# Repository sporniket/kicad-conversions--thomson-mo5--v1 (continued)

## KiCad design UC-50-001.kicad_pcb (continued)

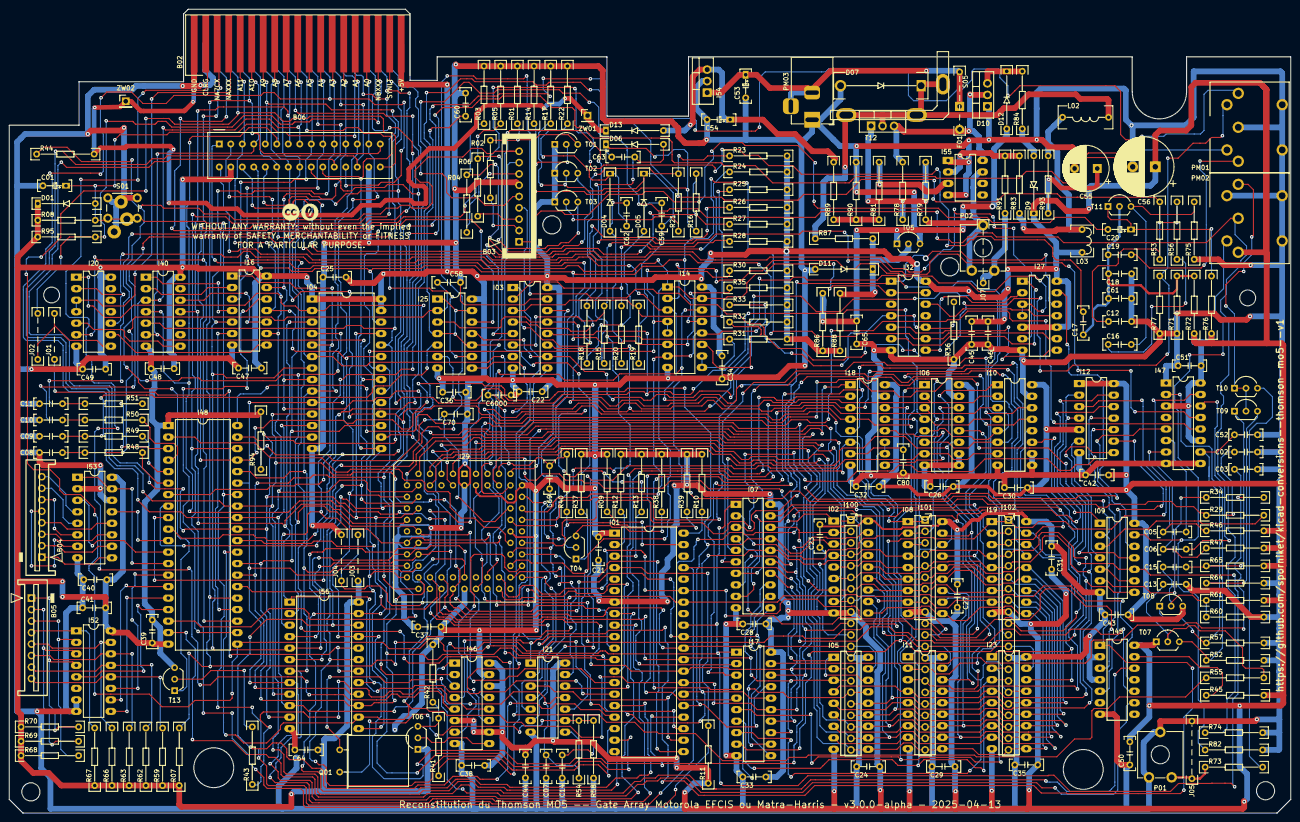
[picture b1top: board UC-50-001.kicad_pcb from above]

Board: 2 copper layers, 283.0 x 177.5 mm, 253 parts (1 on the bottom side), 233 nets.

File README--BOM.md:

# Bill of material

> On A4 sized sheets of paper, best printed using landscape format, zooming at most 75%.

## Capacitors

### Non polarized

|Quantity|Designators|Value|Comment|Suggestion|
|---|---|---|---|---|
|5|C02, C03, C05, C15, C60|100pF|Radial, pitch 5,08mm/200mils|Vishay K101K10X7RH5UH5|
|32|C06, C21, C22, C23, C24, C25, C26, C27, C28, C29, C30, C31, C32, C33, C34, C35, C36, C37, C38, C39, C40, C41, C42, C43, C44, C45, C46, C47, C48, C49, C50, C51|47nF|Radial, pitch 5,08mm/200mils|Vishay K473K10X7RF5UH5|
|2|C07, C14|120pF|Radial, pitch 5,08mm/200mils|Vishay K121K10X7RF5UH5|
|7|C08, C09, C10, C11, C16, C17, C19|220nF|Radial, pitch 5,08mm/200mils|Vishay K224K20X7RF5TH5|
|2|C12, C61|6.8nF|Radial, pitch 5,08mm/200mils|Vishay K682K10X7RH5UH5|
|1|C13|1nF|Radial, pitch 5,08mm/200mils|Vishay K102K10X7RH5UH5|
|1|C18|10nF|Radial, pitch 5,08mm/200mils|Vishay K103K15X7RF5UH5|
|1|C52|2.2uF|Radial, pitch 5,08mm/200mils|TDK FG28X5R1E225KRT06|
|1|C59|18pF|Radial, pitch 5,08mm/200mils|Vishay K180J15C0GF5TH5|


### Polarized

Electrolytic capacitors.

|Quantity|Designators|Value|Comment|Suggestion|
|---|---|---|---|---|
|2|C01, C53|100uF|Radial, Pitch 5,08mm/200mils|Wurth Elektronik 860020473008|
|2|C04, C20|4.7uF|Radial, Pitch 5,08mm/200mils|Wurth Elektronik 860020472001|
|2|C54, C57|10uF|Radial, Pitch 5,08mm/200mils|Wurth Elektronik 860020472003 |
|1|C55|470uF|Radial, Diameter 10mm, Pitch 5mm|Wurth Elektronik 860020474014|
|1|C56|1000uF|Radial, Diameter 13mm, Pitch 5mm|Wurth Elektronik 860020475018|


## Diodes

|Quantity|Designators|Value|Comment|Suggestion|
|---|---|---|---|---|
|6|D01, D03, D04, D05, D06, D08|1N4148|Horizontal mount, pitch 500mils|Onsemi/Fairchild 1N4148-T26A|
|1|D02|BZX46C12|Horizontal mount, pitch 500mils|Vishay Semiconductors BZX55C12-TAP|
|1|D07|BYW98-100|Horizontal mount, pitch 700mils ; the body hangs in the air, at least 1cm appart from the PCB|Diodes incorporated 1N5401G-T|


## Inductors

|Quantity|Designators|Value|Comment|Suggestion|
|---|---|---|---|---|
|1|L01|150nH|Coated leaded inductor|Bourns 78FR15M-RC|
|1|L02|350uH|Ferrite core inductor||
|1|L03|15uH|Ferrite core inductor||

## Crystal oscillator

|Quantity|Designators|Value|Comment|Suggestion|
|---|---|---|---|---|
|1|Q01|16MHz|HC49-U format, horizontal mounting|Abracon AB-16.000MHZ-B2|

## Resistors

> Unless stated otherwise, mounting is horizontal with a pitch of 500 mils.

|Quantity|Designators|Value|Comment|Suggestion|
|---|---|---|---|---|
|19|R01, R03, R05, R10, R30, R31, R32, R33, R35, R42, R48, R49, R50, R51, R52, R56, R77, R78, R82|1KΩ||YAGEO MFR-25FTE52-1K|
|4|R02, R04, R06, R41|68Ω||YAGEO MFR-25FTE52-68R|
|2|R07, R36|680Ω||YAGEO MFR-25FTE52-680R|
|2|R08, R71|100KΩ||YAGEO MFR-25FTE52-100K|
|1|R09|220Ω||YAGEO MFR-25FTE52-220R|
|3|R11, R12, R13|3K3Ω||YAGEO MFR-25FTE52-3K3|
|14|R14, R17, R22, R45, R46, R47, R59, R62, R63, R66, R67, R68, R69, R70|10KΩ||YAGEO MFR-25FTE52-10K|
|3|R15, R18, R20|3KΩ||YAGEO MFR-25FTE52-3K|
|7|R16, R19, R21, R39, R44, R54, R58|22KΩ||YAGEO MFR-25FTE52-22K|
|8|R23, R24, R25, R26, R27, R28, R40, R43|4K7Ω||YAGEO MFR-25FTE52-4K7|
|3|R29, R34, R38|100Ω||YAGEO MFR-25FTE52-100R|
|1|R37|75Ω||YAGEO MFR-25FTE52-75R|
|2|R53, R61|33KΩ||YAGEO MFR-25FTE52-33K|
|1|R55|24KΩ||YAGEO MFR-25FTE52-24K|
|1|R57|820Ω||YAGEO MFR-25FTE52-820R|
|1|R60|330KΩ||YAGEO MFR-25FTE52-330K|
|1|R64|180Ω||YAGEO MFR-25FTE52-180R|
|1|R65|2K7Ω||YAGEO MFR-25FTE52-2K7|
|1|R72|39KΩ|Vertical mounting, pitch 200mils|YAGEO MFR-25FTE52-39K|
|1|R73|47Ω||YAGEO MFR-25FTE52-47R|
|1|R74|390Ω||YAGEO MFR-25FTE52-390R|
|2|R75|15KΩ||YAGEO MFR-25FTE52-15K, KOA Speer MF1/4CCT52R1502F|
|1|R76|3K9Ω||YAGEO MFR-25FTE52-3K9|
|1|R79|1K5Ω||YAGEO MFR-25FTE52-1K5|
|1|R80|27KΩ||YAGEO MFR-25FTE52-27K|
|2|R81, R83|330Ω||YAGEO MFR-25FTE52-330R|

## Transistors

|Quantity|Designators|Value|Comment|Suggestion|
|---|---|---|---|---|
|8|T01, T02, T03, T06, T07, T09, T10, T11|BC547B|TO-92|Diotec Semiconductor BC547B|
|2|T04, T08|BC557B|TO-92|Diotec Semiconductor BC557B|
|1|T05|BC337-40|TO-92|Diotec Semiconductor BC337-40|
|1|T12|BDX54|TO-220-3|STMicroelectronics BDX54C|

## Integrated Circuits

|Quantity|Designators|Value|Comment|Suggestion Socket|Suggestion IC|Datasheet|
|---|---|---|---|---|---|---|
|1|I01|MC6809EP|DIP 40 W15.24mm|Adam Tech ICS-640-T||https://ia601601.us.archive.org/13/items/bitsavers_motorolad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|
|6|I02, I05, I08, I11, I19, I23|TMS4416 – 16k×4bits DRAM|DIP 18 W7.62mm|Adam Tech ICS-318-T||https://raw.githubusercontent.com/sporniket/kicad-symbols-ge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|
|1|I03|HM7603 32×8 PROM|DIP 16 W7.62mm|Adam Tech ICS-316-T||https://raw.githubusercontent.com/sporniket/kicad-symbols-ge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|
|1|I04|M27128A 16k×8 EPROM|DIP 28 W15.24mm|Adam Tech ICS-628-T||https://pdf.datasheetcatalog.com/datasheet_pdf/sgs-thomson-m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|
|2|I06, I10|74LS173 Registre D 4 bits|DIP 16 W7.62mm|Adam Tech ICS-316-T||https://www.ti.com/lit/ds/symlink/sn54ls173a.pdf|
|2|I07, I17|74LS245 – Bus transceiver|DIP 20 W7.62mm|Adam Tech ICS-320-T||https://www.ti.com/lit/ds/symlink/sn54ls245-sp.pdf|
|1|I09|74LS32 – 4× 2-input OR gates|DIP 14 W7.62mm|Adam Tech ICS-314-T||https://www.ti.com/lit/ds/symlink/sn74ls32.pdf|
|1|I12|74LS11 – 3×3 inputs AND gates|DIP 14 W7.62mm|Adam Tech ICS-314-T||https://www.ti.com/lit/ds/symlink/sn54ls11.pdf|
|1|I14|74LS156 2×2:4 decoder/demultiplexer|DIP 16 W7.62mm|Adam Tech ICS-316-T||https://www.ti.com/lit/ds/symlink/sn74ls156.pdf|
|2|I16, I21|74LS04 Sextuple inverseur|DIP 14 W7.62mm|Adam Tech ICS-314-T||https://www.ti.com/lit/ds/symlink/sn74ls04.pdf|
|1|I18|74LS165 Sérialiseur 8:1|DIP 16 W7.62mm|Adam Tech ICS-316-T||https://www.ti.com/lit/ds/symlink/sn54ls165a-sp.pdf|
|1|I20|74LS32 4×2 inputs OR gates|DIP 14 W7.62mm|Adam Tech ICS-314-T||https://www.ti.com/lit/ds/symlink/sn74ls32.pdf|
|1|I25|74LS126 Quadruple tampon de bus|DIP 14 W7.62mm|Adam Tech ICS-314-T||https://www.ti.com/lit/ds/symlink/sn54ls125a.pdf|
|1|I27|DM7486N 4×2 inputs XOR gates|DIP 14 W7.62mm|Adam Tech ICS-314-T||https://www.ti.com/lit/ds/symlink/sn54s86.pdf|
|1|I29|Gate array Motorola MC1300|Staggered PLCC68 with keyhole||||
|1|I32|74X20 2×4 inputs NAND gates|DIP 14 W7.62mm|Adam Tech ICS-314-T||https://www.ti.com/lit/ds/symlink/sn74ls20.pdf|
|1|I40|74LS30 8 inputs NAND gate|DIP 14 W7.62mm|Adam Tech ICS-314-T||https://www.ti.com/lit/ds/symlink/sn5430.pdf|
|1|I45|74LS74 Double Flip-Flop 'D'|DIP 14 W7.62mm|Adam Tech ICS-314-T||https://www.ti.com/lit/ds/sdls119/sdls119.pdf|
|1|I46|74LS157 4×2:1 Multiplexeur|DIP 16 W7.62mm|Adam Tech ICS-316-T||https://www.ti.com/lit/ds/symlink/sn54157.pdf|
|1|I47|74LS211 Double multi-vibrateur monostable|DIP 16 W7.62mm|Adam Tech ICS-316-T||https://www.ti.com/lit/ds/symlink/sn74221.pdf|
|1|I48|MC6821 Peripheral Interface Adapter|DIP 40 W15.24mm|Adam Tech ICS-640-T||https://d148k72crfmm2d.cloudfront.net/wp-content/uploads/201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|
|1|I52|74LS151 MULTIPLEXER|DIP 16 W7.62mm|Adam Tech ICS-316-T||https://www.ti.com/lit/ds/symlink/sn74ls151.pdf|
|1|I53|74LS156 DEMULTIPLEXER|DIP 16 W7.62mm|Adam Tech ICS-316-T||https://www.ti.com/lit/ds/symlink/sn74ls156.pdf|
|1|I54|L78L05 TO92|TO-92||STMicroelectronics L78L05ABZ|http://www.st.com/content/ccc/resource/technical/document/da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|
|1|I55|LM311N Comparateur différentiel|DIP 8 W7.62mm|Adam Tech ICS-308-T||https://www.ti.com/lit/ds/symlink/lm211.pdf|

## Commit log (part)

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2022-11-08 fixed directions on using README-template.md
2022-11-08 readme template : rephrase licence to mention CC0, simplify 'how to use' section
2022-11-08 adjust the mention of what was used to make the project
2023-05-12 update submodules
2023-05-12 place les principaux circuits -- il manque le symbole pour le PIA MC6821
2023-05-12 upgrade kicad-symbol-generated to 2.5.0 -- added PIA
2023-05-12 ajuste position des signaux globaux
2023-05-13 cpu : sépare le circuit reset du pull-up de la broche 34
2023-05-13 Assure la bonne attribution a dcmoto des fichiers de référence
2023-05-13 fix data and address bus label
2023-05-13 done I29, fixed address/databus mapping
2023-05-13 commence PIA
2023-05-13 fin provisoire du PIA
2023-05-14 RAM : temporairement fini
2023-05-14 provisionne une feuille pour le système d'horloges
2023-05-14 Port LEP : report des voltages
2023-05-14 remise au propre
2023-05-14 définit le répertoire d'export
2023-05-15 début des horloges
2023-05-15 continue l'horlogerie : 16 MHz
2023-05-17 horloges : stylo optique
2023-05-18 fix 74x32 symbol ; better visualization from light pen pin 4 to light pen interrupt signal
2023-05-18 cadencement -- arrangement visuel
2023-05-18 Point de test 1
2023-05-18 renomme fiche video
2023-05-18 Nommage de signaux d'après documentations techniques
2023-05-19 prepare feuille circuit video
2023-05-19 retravaille les ports LEP et crayon optique pour correspondre visuellement (suppression de renversements)
2023-05-20 update generated symbols libraries
2023-05-21 continue le circuit vidéo
2023-05-21 bouge I21 vers la page du processeur
2023-05-24 ports d'extension et cartouche
2023-05-24 fini eprom, réarrange la feuille, version alpha
2023-05-24 prepare release
2023-06-24 fixes DRC : duplicate, designators with '?'
2023-07-01 scans of the board
2023-07-04 schematic : mounting holes
2023-07-06 update footprints libraries
2023-07-06 update footprint libraries
2023-07-07 created cartridge footprint and associated with symbol in schematics
2023-07-07 associate extension ports with their footprints
2023-07-08 updated footprints: thomson MO-TO extension port backside -- added '(NC)' label to not connected pad
2023-07-08 footprint for D07
2023-08-06 Added footprint : Thomson MO-TO gate array a PLCC68 socket, with staggered pins and key hole
2023-08-06 fixed thomson extension port backside : pin 1 is named '+12V', not 'ZW02'
2023-09-29 setup background image to create pcb
2023-11-01 assign footprints to L01 and Q01
2023-11-04 created and assigned footprints : keyboard and video connectors ; standard barrel-jack ; 6mm standard push button ; trimpot
2023-11-04 starting component placement
2023-11-04 fixed : S01 footprint
2023-11-04 placement : RAM
2023-11-04 placement of various components 2023-11-04T08:53:52+01:00
2023-11-04 done placing component, but there are missing pull-ups for the keyboard port
2023-11-04 added missing R35, R59, R62, R63, R66~R70
2023-11-04 bump publication date of schematics
2023-11-18 pcb session 2023-11-18T07:44:34+01:00 : changed transistor symbols to swap pins ; there is something wrong with the gate array, even 180° rotation does not fix
2023-11-18 pcb session 2023-11-18T08:10:40+01:00 : Gate array problem solved, it has to be put on the bottom side
2023-11-18 pcb session 2023-11-18T15:24:48+01:00
2023-11-18 pcb session 2023-11-18T16:09:41+01:00
2023-11-23 pcb session 2023-11-23T22:43:45+01:00
2023-11-30 added reference pictures of the motherboard -- component side
2023-12-01 pcb session 2023-12-01T20:37:50+01:00 -- fix transistor symbols, trace south-west quadrant
2023-12-02 pcb session 2023-12-02T21:14:25+01:00
2023-12-03 pcb session 2023-12-03T05:02:30+01:00 : change DIN5 footprints
2023-12-03 pcb session 2023-12-03T22:57:14+01:00
2023-12-04 pcb session 2023-12-04T23:00:10+01:00
2023-12-15 pcb session 2023-12-15 -- I32
2023-12-15 pcb session 2023-12-15T23:21:59+01:00 -- around I27
2023-12-16 pcb session 2023-12-16T22:54:14+01:00
2024-01-13 pcb session 2024-01-13T07:08:26+01:00
2024-03-10 Fixes R20, R21, R22
2024-03-11 Change T12 symbol (pin assigment, EBC to BCE) and footprint (TO-92 inline vertical to TO-220-3 vertical)
2024-03-17 fixed : add thermal switch between +15V and T12, add heatsink
2024-03-17 adjust the footprint of the heatsink, and the voltage source of I55
2024-03-20 fixed C55 connections in schematics to match traces, fixed power symbols names on schematics, and reassign correct nets instead of '+15V'
2024-03-21 prepare next version
2024-03-23 pcb session 2024-03-23T07:29:41+01:00
2024-03-23 pcb session 2024-03-23T11:56:01+01:00 -- renumbered shield pin as 'SH'
2024-03-23 pcb session 2024-03-23T22:49:18+01:00
2024-03-24 pcb session 2024-03-24T08:04:18+01:00 -- routing, I20[12,13] to be left unwired
2024-03-28 rework of connector B03 : footprint, direction on PCB
2024-03-28 update B04/B05 footprint
2024-03-28 adjust schematics of color to video port
2024-03-29 pcb session 2024-03-29T07:00:55+01:00 -- finished I03,I06,I10,I18,I25
2024-03-29 pcb session 2024-03-29T09:23:57+01:00 -- I11
2024-03-30 pcb session 2024-03-30T07:45:55+01:00 -- net I11-B, fixed net couleur_tour.rt
2024-03-30 pcb session 2024-03-30T08:46:30+01:00 -- I07, I01
2024-03-30 pcb session 2024-03-30T15:12:14+01:00 -- done I21
2024-03-30 pcb session 2024-03-30T15:29:34+01:00 -- done I16
2024-03-31 pcb session 2024-03-31T11:28:26+02:00 -- done I14, I20, I27, I32, I40
2024-03-31 pcb session 2024-03-31T11:44:40+02:00 -- doing gate array I29
2024-03-31 note on the schematic about pin 64 of I29
2024-03-31 note about P01
2024-03-31 pcb session 2024-03-31T18:29:45+02:00 -- doing 16MHz, video and light pen cadencing circuit
2024-03-31 pcb session 2024-03-31T21:16:32+02:00 -- doing 16MHz, video and light pen cadencing circuit
2024-03-31 pcb session 2024-03-31T22:43:45+02:00 -- done 16MHz, video and light pen cadencing circuit
2024-03-31 pcb session 2024-03-31T23:08:16+02:00 -- done I48, I52, I53, B04, B05, PM01, PM02
2024-03-31 prepare next alpha
2024-04-07 pcb session 2024-04-07T07:45:23+02:00 -- done GND + missing wire R38-T04#3
2024-04-07 pcb session 2024-04-07T11:09:01+02:00 -- some DRC fixes : missing connection, one via dimensions
2024-04-12 pcb session 2024-04-12T23:35:43+02:00 -- DRC -- remade all the vias
2024-04-13 pcb session 2024-04-13T08:12:14+02:00 -- silkscreen -- from left to the line made by (C20,C48)
2024-04-13 pcb session 2024-04-13T08:15:30+02:00 -- silkscreen -- Show project URL
2024-04-14 Fix directions about moding the cartridge port : fixed E and R/*W wiring
2024-04-14 Fix directions about moding the cartridge port : fixed footprint on pcb
2024-04-14 pcb session 2024-04-14T16:37:39+02:00 -- back silkscreen -- indication to mod cartridge port for nanoreseau compatibility
2024-04-19 pcb session 2024-04-19T09:07:25+02:00 -- bottom side -- copper pours +5V +18V
2024-04-20 pcb session 2024-04-20T11:08:01+02:00 -- copper pours +5V up -- the left border
2024-04-20 pcb session 2024-04-20T15:38:57+02:00 -- tweaked trace to PM03 on front side
2024-04-20 prepare next release -- markings
2024-05-26 start working on the BOM
2024-05-26 BOM -- Add mounting description in comments for diodes
2024-06-01 BOM -- suggest polarized capacitors
2024-06-01 BOM -- inductors
2024-06-02 Issue #1 -- Small corrections for beta2 -- wider lateral chamfers for extension connector, set to 1mm along x and y axis
2024-06-02 Issue #1 -- Small corrections for beta2 -- exclude copper pour around internal mounting holes (front layer)
2024-06-02 Issue #1 -- Small corrections for beta2 -- tweak the width of the pads of the extension connector, from 2mm to 1.5mm
2024-06-07 Issue #2 -- Small enhancements for beta2 -- enlarge vias for modding cartridge port to get E and R/W + fixes DRC
2024-06-07 Issue #2 -- Small enhancements for beta2 -- Schematic -- D02 value becomes 'BZX46C12'
2024-06-07 excludes some DRC violations that won't be a problem
2024-06-09 Issue #2 -- Small enhancements for beta2 -- Reset switch -- ad-hoc footprint to combine regular switch with the original reset button footprint
2024-06-11 BOM -- list of crystal oscilators, resistors, transistors and ICs
2024-06-29 start adding measurement to PCB
2024-06-29 dummy pcb to test the cartridge port
2024-07-01 BOM -- done transistors, prepare ICs
2024-07-02 BOM -- IC sockets and L78L05
2024-07-02 BOM -- reorder columns for ICs
2024-07-02 BOM -- recommended printing settings
2024-07-31 rework pcb edge for measurements
2024-07-31 finished measurements
2024-11-01 drc exclusion : starved thermal, courtyards overlap
2024-11-06 DRC exclusions
2024-11-11 Issue #3 -- Tie I55.1 to GND
2024-11-17 Reworked power supply circuitry : resistors value, schematic layout
2024-11-17 adjust layout of power supply subsheet
2024-11-17 one ignored starved thermal link is fixed at I32
2024-11-25 Resolves #4 : Fix reset circuit
2024-12-30 Resolves #5 : extends the extension port by 2mm
2024-12-30 prepare release : issue date
2024-12-30 prepare release : README
2024-12-30 Area refill
2024-12-30 Prepare release again
2025-02-02 prepare forking to create the version with EFCIS gate array
2025-02-02 subsheet_100 -- change values of C01, R08
2025-02-08 subsheet 101 -- change to gate array EFCIS
2025-02-08 Resolves #11 : [ga efcis][schematics] Rewire I16 and I21
2025-02-08 I29 pin 57 -- pulled down with R94
2025-02-08 done j03/J04
2025-02-08 I29 -- Replace symbole with correct one (pin 34, pin 36)
2025-02-15 Resolves #16 : [ga efcis] Supplemental EPROM I56 (27c32) ; Fixed orientation and updated the cartridge port too
2025-02-15 update the symbol of gate array I29
2025-02-15 Various mentions, added C60bis to I29 on pin 62
2025-02-15 fixes second EPROM designator, name of subsheet 104
2025-03-01 start reworking power supply
2025-03-01 connect 12V to B01#1 and ZW02
2025-03-01 start doing the +5V circuit
2025-03-01 done power supply circuit
2025-03-22 Confirmed value of R84 : 100
2025-04-12 pcb : setup new backdrops for front and back layers
2025-04-12 pcb : (start) moving components, south-west corner
2025-04-12 pcb : moving components, west side
2025-04-12 pcb : moving components, south-west corner, south border
2025-04-12 pcb : moving components, south border
2025-04-13 pcb : moved components, south-border around I01
2025-04-13 pcb : moved components, middle north around I25, I03, I14
2025-04-13 fixed power net names confusion
2025-04-13 pcb : moved component, north side to middle next to I14
2025-04-13 pcb : removed all copper pours, and almost all traces
2025-04-13 pcb : moved components, south-east corner, fixed links between P01 and J05
2025-04-13 pcb : moved components, south-east corner, column of resistors
2025-04-13 pcb : moved components, middle-east area, I18, I06 and I10
2025-04-13 pcb : moved components, middle-east border
2025-04-13 pcb : moved component, middle north-east corner
2025-04-13 pcb : done, fixed CLTV circuitry
2025-04-19 Done #20 : missing capacitors C65, C69, C70, C80 (footprints on PCB, not found on schematics)
2025-04-20 pcb : 16MHz clocking circuit
2025-04-20 pcb : B05
2025-04-21 pcb : traces of B05
2025-04-21 pcb : traces of I52, plus some +5V
2025-04-21 pcb : trace I53
2025-04-21 pcb : traces around PM02
2025-04-24 pcb : j/reset and i/firq
2025-04-27 pcb : around DRAM chips
2025-09-27 fixed backdrops for better alignement
2025-09-27 [pcb] fixed area F.3
2025-09-27 [pcb] fixed area F.2
2025-09-28 [pcb] fixed area F.0
2025-09-28 [pcb] rework area A.1
2025-09-28 [pcb] fixed position of gate array
2025-09-28 [pcb] area A.2, A.3
2025-09-28 [pcb] area A.2
2025-09-28 [pcb] Area B.0, B.1, C.0
2025-09-29 [pcb] area B.*, C.0, C.1
2025-09-30 fixed I45 : pin 2 and 4 are now grounded
2025-09-30 done extension port, cartridge port
2025-10-01 [pcb] fixed positionning D.0, D.1, and partially D.2
2025-10-01 [pcb] fixed positionning areas D.0, D.1, E.0, E.1, partially D.2, E.2
2025-10-01 [pcb] Around the gate array
2025-10-02 Done gate-array, updated some disconnections from pcb into schematic
2025-10-02 [pcb] north-west area
2025-10-03 more notes on the gate array and not connected power pins
2025-10-03 [pcb] slowly connect everything from the north
2025-10-04 [pcb] almost done
2025-10-04 [schematic] the pcb tell that synlt does not go to I46
2025-10-04 update layer display
2025-10-05 [pcb] silkscreen, area B.*
2025-10-05 [pcb] silkscreen, area C.*
2025-10-05 [pcb] silkscreen, area D.*
2025-10-05 [pcb] silkscreen, area E.*
